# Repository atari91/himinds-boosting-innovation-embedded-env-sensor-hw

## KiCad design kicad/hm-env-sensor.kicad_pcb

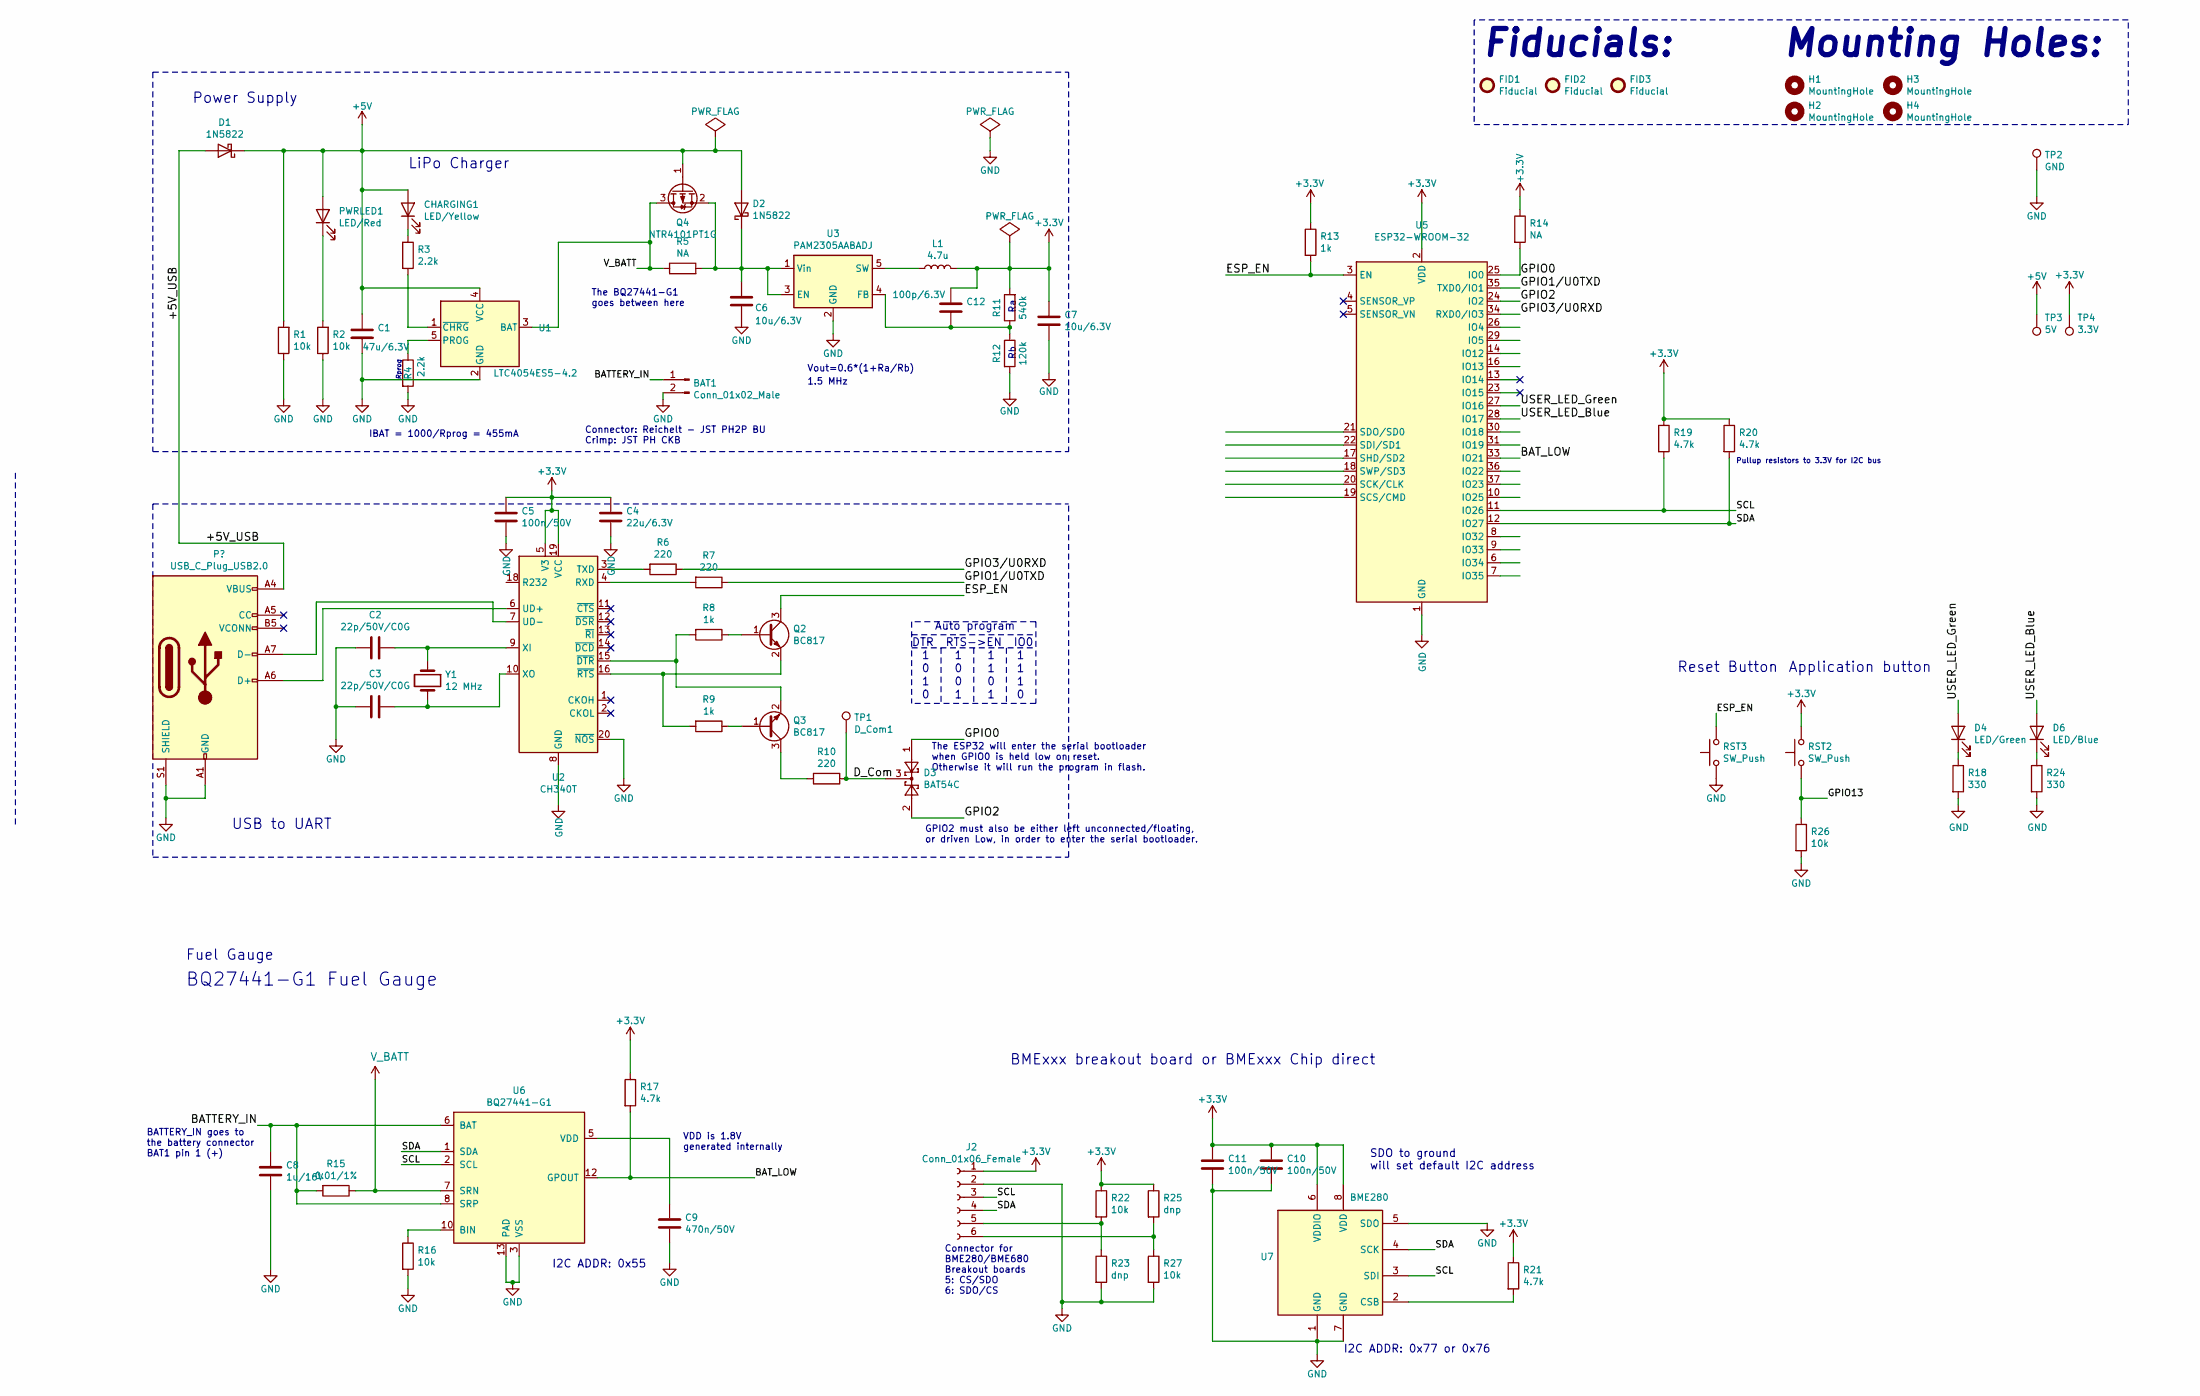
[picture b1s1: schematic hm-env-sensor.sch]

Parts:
BAT1: Conn_01x02_Male; JST_PH_S2B-PH-K_1x02_P2.00mm_Horizontal; Part Nr. JST PH2P ST90
C1: 47u/6.3V; C_0805_2012Metric_Pad1.15x1.40mm_HandSolder
C2, C3: 22p/50V/C0G; C_0603_1608Metric_Pad1.05x0.95mm_HandSolder
C4: 22u/6.3V; C_0603_1608Metric_Pad1.05x0.95mm_HandSolder
C5, C10, C11: 100n/50V; C_0603_1608Metric_Pad1.05x0.95mm_HandSolder
C6, C7: 10u/6.3V; C_0805_2012Metric_Pad1.15x1.40mm_HandSolder
C8: 1u/16V; C_0603_1608Metric_Pad1.05x0.95mm_HandSolder
C9: 470n/50V; C_0603_1608Metric_Pad1.05x0.95mm_HandSolder
C12: 100p/6.3V; C_0805_2012Metric_Pad1.15x1.40mm_HandSolder
CHARGING1: LED/Yellow; LED_0603_1608Metric_Pad1.05x0.95mm_HandSolder
D1, D2: 1N5822; D_SMC_Handsoldering
D3: BAT54C; SOT-23
D4: LED/Green; LED_0603_1608Metric_Pad1.05x0.95mm_HandSolder
D6: LED/Blue; LED_0603_1608Metric_Pad1.05x0.95mm_HandSolder
FID1, FID2, FID3: Fiducial; Fiducial_1mm_Mask2mm
H1, H2, H3, H4: MountingHole; MountingHole_3.2mm_M3
J2: Conn_01x06_Female; PinSocket_1x06_P2.54mm_Vertical
L1: 4.7u; L_Wuerth_WE-TPC-3816; Part Nr. WUE 744031004
PWRLED1: LED/Red; LED_0603_1608Metric_Pad1.05x0.95mm_HandSolder
Q2, Q3: BC817; SOT-23
Q4: NTR4101PT1G; SOT-23; Part. Nr. NTR4101PT1G
R1, R2, R16, R22, R26, R27: 10k; R_0603_1608Metric_Pad1.05x0.95mm_HandSolder
R3, R4: 2.2k; R_0603_1608Metric_Pad1.05x0.95mm_HandSolder
R5, R14: NA; R_0603_1608Metric_Pad1.05x0.95mm_HandSolder
R6, R7, R10: 220; R_0603_1608Metric_Pad1.05x0.95mm_HandSolder
R8, R9, R13: 1k; R_0603_1608Metric_Pad1.05x0.95mm_HandSolder
R11: 540k; R_0603_1608Metric_Pad1.05x0.95mm_HandSolder
R12: 120k; R_0603_1608Metric_Pad1.05x0.95mm_HandSolder
R15: 0.01/1%; R_1206_3216Metric_Pad1.42x1.75mm_HandSolder
R17, R19, R20, R21: 4.7k; R_0603_1608Metric_Pad1.05x0.95mm_HandSolder
R18, R24: 330; R_0603_1608Metric_Pad1.05x0.95mm_HandSolder
R23, R25: dnp; R_0603_1608Metric_Pad1.05x0.95mm_HandSolder
RST2, RST3: SW_Push; SW_SPST_PTS645
TP1: D_Com1; TestPoint_THTPad_D2.0mm_Drill1.0mm
TP2: GND; TestPoint_THTPad_D2.0mm_Drill1.0mm
TP3: 5V; TestPoint_THTPad_D2.0mm_Drill1.0mm
TP4: 3.3V; TestPoint_THTPad_D2.0mm_Drill1.0mm
U1: LTC4054ES5-4.2; TSOT-23-5; Part Nr. LTC4054ES5-4.2TRMP
U2: CH340T; SSOP-20_5.3x7.2mm_P0.65mm
U3: PAM2305AABADJ; TSOT-23-5; Part Nr. PAM2305AABADJ
U5: ESP32-WROOM-32
U6: BQ27441-G1; Texas_S-PDSO-N12
U7: BME280; Bosch_LGA-8_2.5x2.5mm_P0.65mm_ClockwisePinNumbering
Y1: 12 MHz; Crystal_SMD_HC49-SD_HandSoldering; Part Nr. GEY KX-KST SMDC

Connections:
+3V3: C4.1, C5.1, C7.1, C10.1, C11.1, C12.1, J2.1, L1.2, R11.2, R13.1, R14.1, R17.1, R19.1, R20.1, R21.1, R22.1, R25.1, RST2.2, TP4.1, U2.5 (V3), U2.19 (VCC), U5.2 (VDD), U7.6 (VDDIO), U7.8 (VDD)
+5V: C1.1, CHARGING1.2 (A), D1.1 (K), D2.2 (A), PWRLED1.2 (A), Q4.1 (G), R1.2, TP3.1, U1.4 (VCC)
/+5V_USB: D1.2 (A); also elsewhere on the board
/BATTERY_IN: BAT1.1, C8.1, R15.2, U6.6 (BAT), U6.8 (SRP)
/BAT_LOW: R17.2, U5.33 (IO21), U6.12 (GPOUT)
/D_Com: D3.3, R10.1, TP1.1
/ESP_EN: Q2.3 (C), R13.2, RST3.2, U5.3 (EN)
/GPIO0: D3.1, R14.2, U5.25 (IO0)
/GPIO1/U0TXD: R7.1, U5.35 (TXD0/IO1)
/GPIO2: D3.2, U5.24 (IO2)
/GPIO3/U0RXD: R6.1, U5.34 (RXD0/IO3)
/GPIO13: R26.1, RST2.1
/SCL: J2.3, R19.2, U5.11 (IO26), U6.2 (SCL), U7.3 (SDI)
/SDA: J2.4, R20.2, U5.12 (IO27), U6.1 (SDA), U7.4 (SCK)
/USER_LED_Blue: D6.2 (A), U5.28 (IO17)
/USER_LED_Green: D4.2 (A), U5.27 (IO16)
GND: BAT1.2, C1.2, C2.2, C3.2, C4.2, C5.2, C6.2, C7.2, C8.2, C9.2, C10.2, C11.2, J2.2, R1.1, R2.1, R4.2, R12.2, R16.2, R18.2, R23.2, R24.2, R26.2, R27.2, RST3.1, TP2.1, U1.2 (GND), U2.8 (GND), U2.20 (~NOS), U3.2 (GND), U5.1 (GND), U5.15 (GND), U5.38 (GND), U5.39 (GND), U6.3 (VSS), U6.13 (PAD), U7.1 (GND), U7.5 (SDO), U7.7 (GND); also elsewhere on the board
unnamed: C2.1, U2.9 (XI), Y1.1
unnamed: C3.1, U2.10 (XO), Y1.2
unnamed: C6.1, D2.1 (K), Q4.2 (S), R5.2, U3.1 (Vin), U3.3 (EN)
unnamed: C9.1, U6.5 (VDD)
unnamed: C12.2, R11.1, R12.1, U3.4 (FB)
unnamed: CHARGING1.1 (K), R3.1
unnamed: D4.1 (K), R18.1
unnamed: D6.1 (K), R24.1
unnamed: J2.5, R22.2, R23.1
unnamed: J2.6, R25.2, R27.1
unnamed: L1.1, U3.5 (SW)
unnamed 28: U2.6 (UD+); also elsewhere on the board
unnamed 29: U2.7 (UD-); also elsewhere on the board
unnamed: PWRLED1.1 (K), R2.2
unnamed: Q2.1 (B), R8.1
unnamed: Q2.2 (E), R9.2, U2.16 (~RTS)
unnamed: Q3.1 (B), R9.1
unnamed: Q3.2 (E), R8.2, U2.15 (~DTR)
unnamed: Q3.3 (C), R10.2
unnamed: R3.2, U1.1 (~CHRG)
unnamed: R4.1, U1.5 (PROG)
unnamed: R6.2, U2.3 (TXD)
unnamed: R7.2, U2.4 (RXD)
unnamed: R16.1, U6.10 (BIN)
unnamed: R21.2, U7.2 (CSB)
V_BATT: Q4.3 (D), R5.1, R15.1, U1.3 (BAT), U6.7 (SRN)

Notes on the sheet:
Fiducials:
I2C ADDR: 0x55
VDD is 1.8V generated internally
BQ27441-G1 Fuel Gauge
Vout=0.6*(1+Ra/Rb)
Power Supply
LiPo Charger
Auto program
DTR RTS->EN IO0
USB to UART
IBAT = 1000/Rprog = 455mA
Rprog
Application button
I2C ADDR: 0x77 or 0x76
Fuel Gauge
Reset Button
SDO to ground will set default I2C address
BATTERY_IN goes to the battery connector BAT1 pin 1 (+)
The BQ27441-G1 goes between here
Pullup resistors to 3.3V for I2C bus
The ESP32 will enter the serial bootloader when GPIO0 is held low on reset. Otherwise it will run the program in flash.
GPIO2 must also be either left unconnected/floating, or driven Low, in order to enter the serial bootloader.
1.5 MHz
Connector: Reichelt - JST PH2P BU Crimp: JST PH CKB
Mounting Holes:
Connector for BME280/BME680 Breakout boards 5: CS/SDO 6: SDO/CS
BMExxx breakout board or BMExxx Chip direct

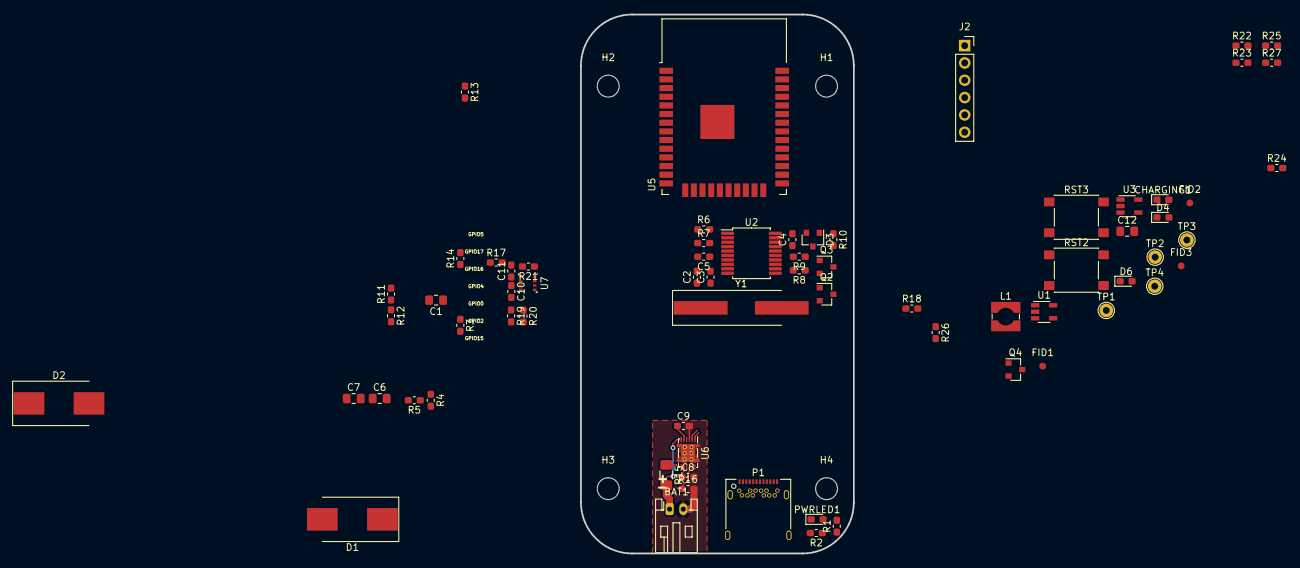
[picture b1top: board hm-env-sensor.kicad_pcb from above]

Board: 2 copper layers, 40.0 x 79.0 mm, 73 parts (0 on the bottom side), 43 nets.

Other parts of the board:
P1: USB_C_Plug_USB2.0; USB_C_Receptacle_Amphenol_12401548E4-2A

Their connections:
/+5V_USB: P1.A4, P1.A9, P1.B4, P1.B9; also elsewhere on the board
GND: P1.A1, P1.A12, P1.B1, P1.B12, P1.S1; also elsewhere on the board
unnamed 28: P1.A6; also elsewhere on the board
unnamed 29: P1.A7; also elsewhere on the board

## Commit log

2020-05-16 replace symbols and footrints by KiCAD libs + simplifiy schematic
2020-05-31 aktuell
